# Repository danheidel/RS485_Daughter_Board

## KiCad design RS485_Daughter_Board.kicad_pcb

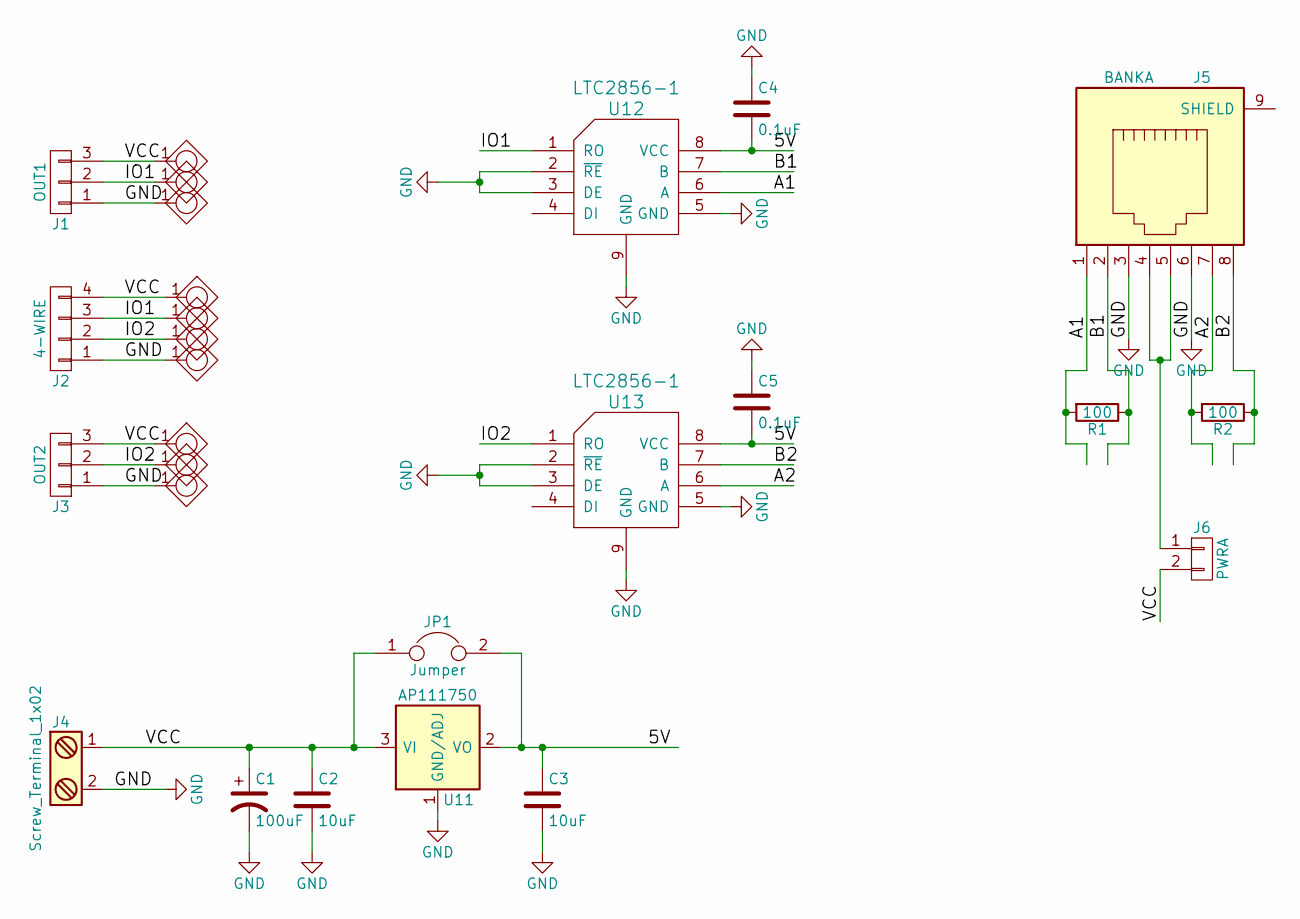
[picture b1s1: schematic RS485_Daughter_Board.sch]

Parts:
C1: 100uF; CP_Radial_D5.0mm_P2.00mm
C2, C3: 10uF; C_1210
C4, C5: 0.1uF; C_0805
J1: OUT1; Pin_Header_Straight_1x03_Pitch2.54mm
J2: 4-WIRE; Pin_Header_Straight_1x04_Pitch2.54mm
J3: OUT2; Pin_Header_Straight_1x03_Pitch2.54mm
J4: Screw_Terminal_1x02; Terminal_Block_Phoenix_SPTAF_Quick_Release_2-Pos_5mm
J5: BANKA; RJ45_8
J6: PWRA; Pin_Header_Straight_1x02_Pitch2.54mm
JP1: Jumper
R1, R2: 100; R_0805
U1, U2, U3, U4, U5, U6, U7, U8, U9, U10: 2mm_thru_hole
U11: AP111750; SOT-223
U12, U13: LTC2856-1; DFN-8-1EP_3x3mm_Pitch0.5mm

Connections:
/5V: C3.1, C4.2, C5.2, JP1.2, U11.2 (VO), U11.4 (VO), U12.8 (VCC), U13.8 (VCC)
/A1: J5.1, R1.2, U12.6 (A)
/A2: J5.7, R2.2, U13.6 (A)
/B1: J5.2, R1.1, U12.7 (B)
/B2: J5.8, R2.1, U13.7 (B)
/IO1: J1.2, J2.3, U2.1, U8.1, U12.1 (RO)
/IO2: J2.2, J3.2, U5.1, U9.1, U13.1 (RO)
/VCC: C1.1, C2.1, J1.3, J2.4, J3.3, J4.1, J6.2, JP1.1, U1.1, U4.1, U7.1, U11.3 (VI)
GND: C1.2, C2.2, C3.2, C4.1, C5.1, J1.1, J2.1, J3.1, J4.2, J5.3, J5.6, U3.1, U6.1, U10.1, U11.1 (GND/ADJ), U12.2 (~RE~), U12.3 (DE), U12.5 (GND), U12.9 (GND), U13.2 (~RE~), U13.3 (DE), U13.5 (GND), U13.9 (GND)
unnamed: J5.4, J5.5, J6.1

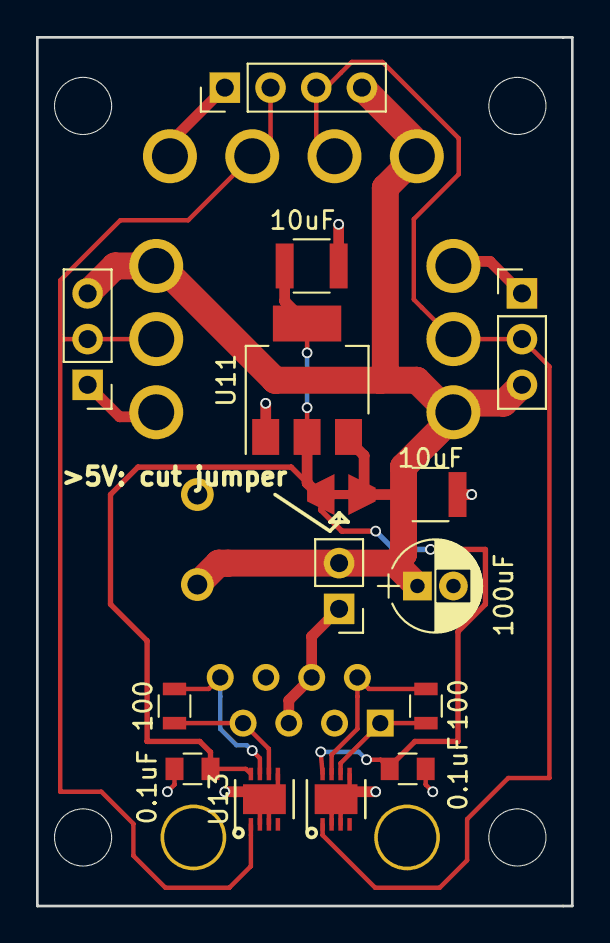
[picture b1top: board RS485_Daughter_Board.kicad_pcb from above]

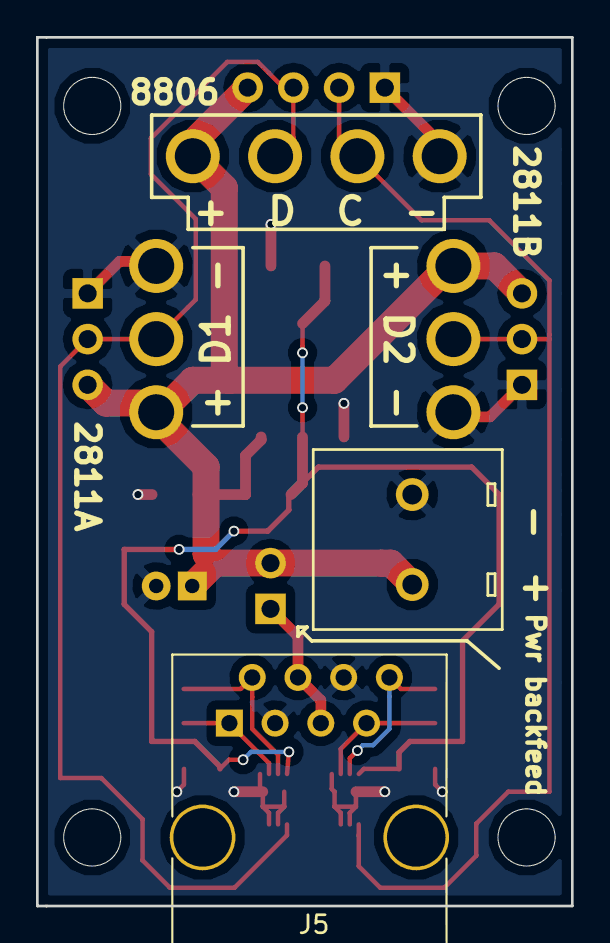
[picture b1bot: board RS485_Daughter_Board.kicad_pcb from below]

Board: 2 copper layers, 29.7 x 48.3 mm, 27 parts (2 on the bottom side), 10 nets.
